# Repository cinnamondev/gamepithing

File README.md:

# Raspberry Pi Handheld (Leviathan)

[Visit the project page!](https://itscinnamon.me/projects/leviathan)

# UPDATE 09/03/2023

This project will likely never be tested or finished now. It is getting increasingly difficult to find a reasonable source of a CM4 to begin and my previously backordered CM4 has since been cancelled without notice.

**Please do not try to make this board, it will probably break something!**

## Loading this project

Clone this project via git
`git clone https://github.com/cinnamondev/gamepithing`

You need Kicad 6+ to load this project.
[KiCad Download](https://www.kicad.org/download/)

## Build it!

Gerber files will be in the releases once this has been properly done- for a BOM read the Wiki (TBD)

## To-do list:
- Snip...

- [ ] Repo clean up
- [ ] CM4 Backorder arrival
- [ ] Extra revisions (general improvements, no additional features)
- [ ] Box/Casing final revision printed (sliding and retention mechanism perfected)
- [ ] Built boards!

## Licensing

Licensed under CERN Open Hardware License v2 - Strongly Reciprocal
[License](LICENSE)

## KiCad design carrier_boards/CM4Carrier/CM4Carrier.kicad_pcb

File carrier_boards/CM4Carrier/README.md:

#   CM4Carrier
Kicad files for the carrier board.

(rev2-slidey): Remaking design to follow best practices.

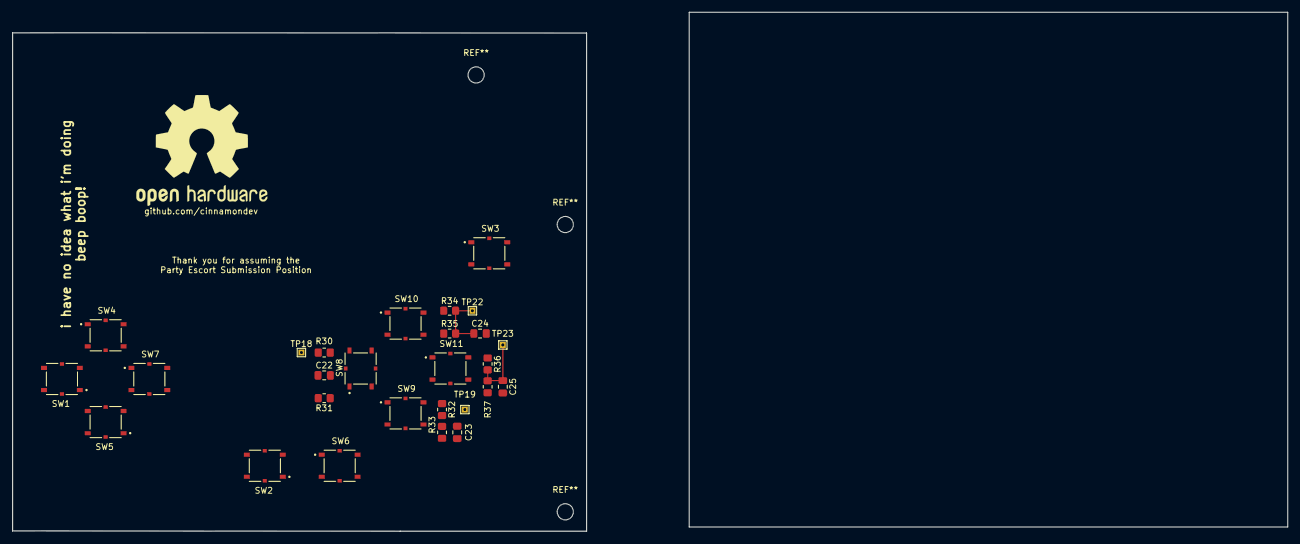
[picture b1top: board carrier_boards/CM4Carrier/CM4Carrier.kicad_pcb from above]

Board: 4 copper layers, 95.9 x 83.3 mm, 27 parts (0 on the bottom side), 10 nets.

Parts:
C22: 100nF; C_0805_2012Metric_Pad1.18x1.45mm_HandSolder
C23, C24, C25: 100n; C_0805_2012Metric_Pad1.18x1.45mm_HandSolder
R30, R32, R34, R36: 1k; R_0805_2012Metric_Pad1.20x1.40mm_HandSolder
R31, R33, R35, R37: 10k; R_0805_2012Metric_Pad1.20x1.40mm_HandSolder
SW1, SW2, SW3, SW4, SW5, SW6, SW7, SW8, SW9, SW10, SW11: SW_Push; SW_PTS526_SMG15_SMTR2_LFS
TP18: A; TestPoint_THTPad_1.0x1.0mm_Drill0.5mm
TP19: X; TestPoint_THTPad_1.0x1.0mm_Drill0.5mm
TP22: B; TestPoint_THTPad_1.0x1.0mm_Drill0.5mm
TP23: Y; TestPoint_THTPad_1.0x1.0mm_Drill0.5mm

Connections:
/3v3: R31.1, R33.1, R35.1, R37.1
/bi6: C22.1, R30.2, R31.2, TP18.1
/bi7: C24.1, R34.2, R35.2, TP22.1
/bi8: C23.1, R32.2, R33.2, TP19.1
/bi9: C25.1, R36.2, R37.2, TP23.1
GND: C22.2, C23.2, C24.2, C25.2, SW1.1, SW2.1, SW3.1, SW4.1, SW5.1, SW6.1, SW7.1, SW8.1, SW9.1, SW10.1, SW11.1
unnamed: R30.1, SW8.2
unnamed: R32.1, SW9.2
unnamed: R34.1, SW10.2
unnamed: R36.1, SW11.2

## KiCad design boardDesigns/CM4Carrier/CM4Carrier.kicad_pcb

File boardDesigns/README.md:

# Board designs

Kicad 6+ is required for these files.
If you want to build this board yourself, I reccomend using the Gerber files built in the Releases section instead. If you want to combine these there are plenty of gerber paneliser softwares available. (Maybe only combine the left shoulder and adaptor as you will likely exceed the JLCPCB sizes).

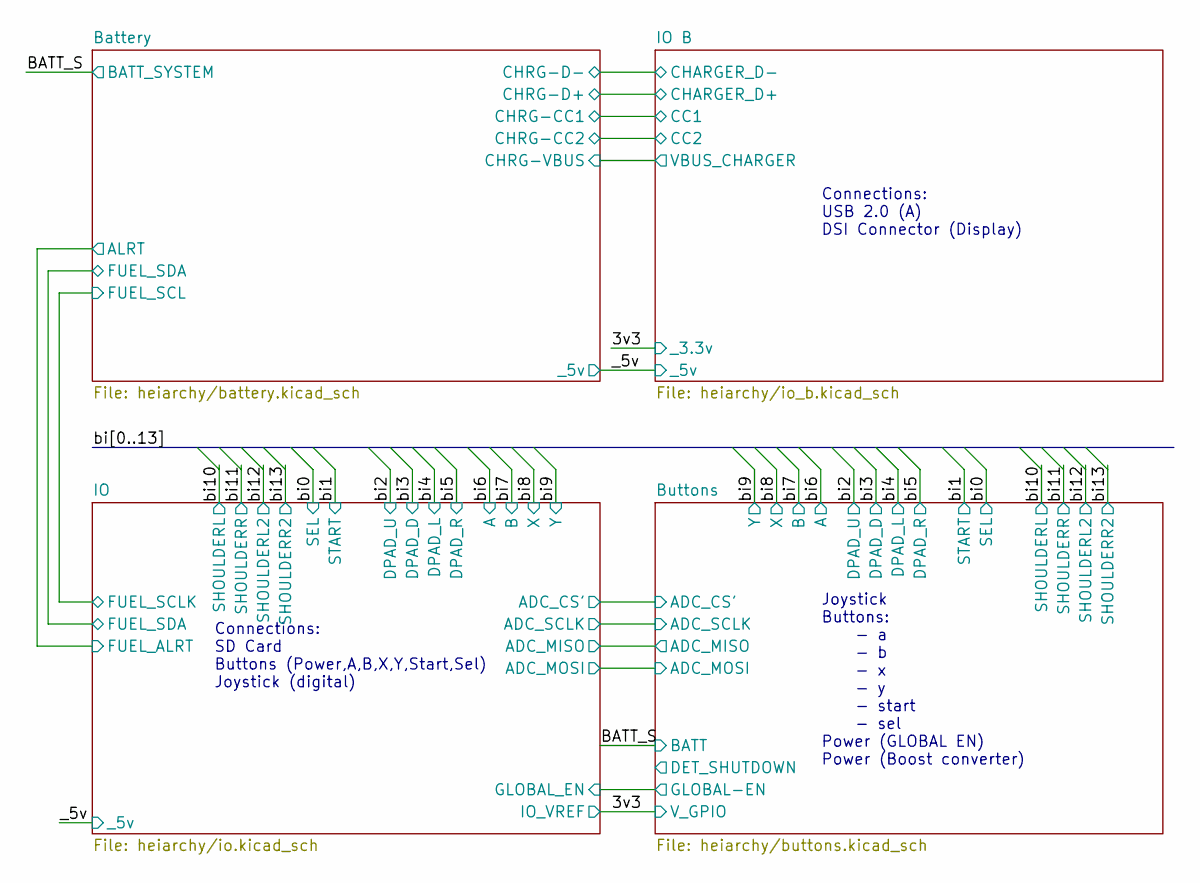
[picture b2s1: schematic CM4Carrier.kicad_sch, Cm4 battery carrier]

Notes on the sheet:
Joystick Buttons: - a - b - x - y - start - sel Power (GLOBAL EN) Power (Boost converter)
Connections: USB 2.0 (A) DSI Connector (Display)
Connections: SD Card Buttons (Power,A,B,X,Y,Start,Sel) Joystick (digital)

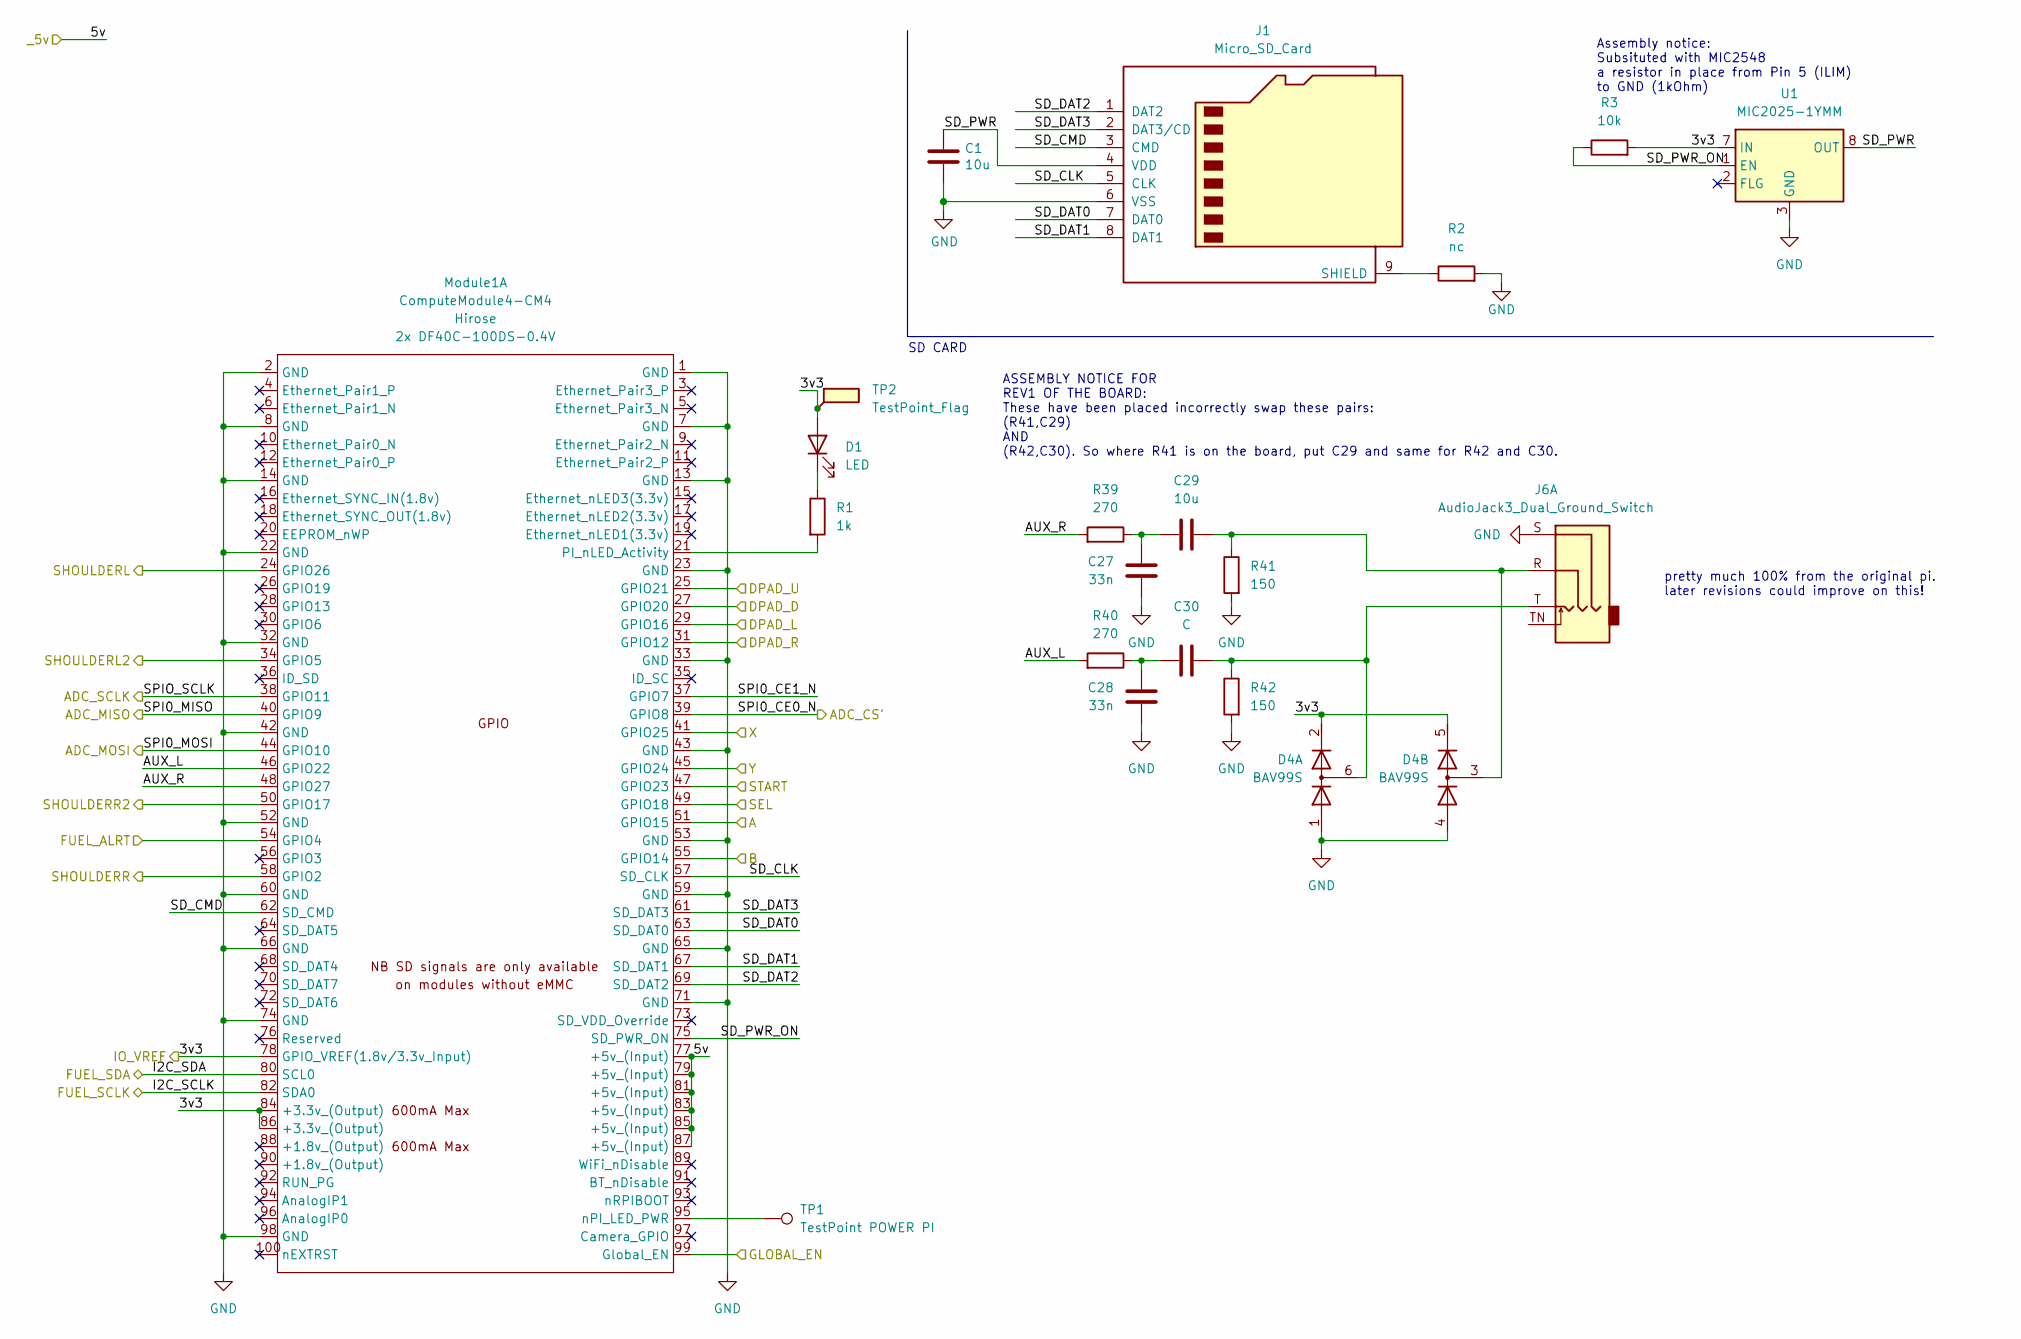
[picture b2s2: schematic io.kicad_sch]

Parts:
C1: 10u; C_0805_2012Metric_Pad1.18x1.45mm_HandSolder; Part Description 10uF 10% 10V Ceramic Capacitor X7R 0805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
C27, C28: 33n; C_0805_2012Metric_Pad1.18x1.45mm_HandSolder
C29: 10u; C_0805_2012Metric_Pad1.18x1.45mm_HandSolder
C30: C; C_0805_2012Metric_Pad1.18x1.45mm_HandSolder
D1: LED; LED_0805_2012Metric_Pad1.15x1.40mm_HandSolder
D4: BAV99S; SOT-363_SC-70-6
J1: Micro_SD_Card; GCT_MEM2067-02-180-00-A_REVB
J6: AudioJack3_Dual_Ground_Switch; Jack_3.5mm_CUI_SJ-3524-SMT_Horizontal
Module1: ComputeModule4-CM4; Raspberry-Pi-4-Compute-Module
R1: 1k; R_0805_2012Metric_Pad1.20x1.40mm_HandSolder
R2: nc; R_0805_2012Metric_Pad1.20x1.40mm_HandSolder
R3: 10k; R_0805_2012Metric_Pad1.20x1.40mm_HandSolder
R39, R40: 270; R_0805_2012Metric_Pad1.20x1.40mm_HandSolder
R41, R42: 150; R_0805_2012Metric_Pad1.20x1.40mm_HandSolder
TP1: TestPoint POWER PI; TestPoint_THTPad_1.0x1.0mm_Drill0.5mm
TP2: TestPoint_Flag; TestPoint_THTPad_1.0x1.0mm_Drill0.5mm
U1: MIC2025-1YMM; MSOP-8_3x3mm_P0.65mm

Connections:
/3v3: D1.2 (A), D4.2 (K2), D4.5 (K4), Module1.78 (GPIO_VREF(1.8v/3.3v_Input)), Module1.84 (+3.3v_(Output)), Module1.86 (+3.3v_(Output)), R3.2, TP2.1, U1.7 (IN); also elsewhere on the board
/Battery/ALRT: Module1.54 (GPIO4); also elsewhere on the board
/Buttons/GLOBAL-EN: Module1.99 (Global_EN); also elsewhere on the board
/IO/AUX_L: Module1.46 (GPIO22), R40.2
/IO/AUX_R: Module1.48 (GPIO27), R39.2
/IO/I2C_SCLK: Module1.82 (SDA0); also elsewhere on the board
/IO/I2C_SDA: Module1.80 (SCL0); also elsewhere on the board
/IO/SD_CLK: J1.5 (CLK), Module1.57 (SD_CLK)
/IO/SD_CMD: J1.3 (CMD), Module1.62 (SD_CMD)
/IO/SD_DAT0: J1.7 (DAT0), Module1.63 (SD_DAT0)
/IO/SD_DAT1: J1.8 (DAT1), Module1.67 (SD_DAT1)
/IO/SD_DAT2: J1.1 (DAT2), Module1.69 (SD_DAT2)
/IO/SD_DAT3: J1.2 (DAT3/CD), Module1.61 (SD_DAT3)
/IO/SD_PWR: C1.1, J1.4 (VDD), U1.6 (OUT), U1.8 (OUT)
/IO/SD_PWR_ON: Module1.75 (SD_PWR_ON), R3.1, U1.1 (EN)
/IO/SPI0_CE0_N: Module1.39 (GPIO8); also elsewhere on the board
/IO/SPI0_CE1_N: Module1.37 (GPIO7)
/IO/SPI0_MISO: Module1.40 (GPIO9); also elsewhere on the board
/IO/SPI0_MOSI: Module1.44 (GPIO10); also elsewhere on the board
/IO/SPIO_SCLK: Module1.38 (GPIO11); also elsewhere on the board
/_5v: Module1.77 (+5v_(Input)), Module1.79 (+5v_(Input)), Module1.81 (+5v_(Input)), Module1.83 (+5v_(Input)), Module1.85 (+5v_(Input)), Module1.87 (+5v_(Input)); also elsewhere on the board
/bi0: Module1.49 (GPIO18); also elsewhere on the board
/bi1: Module1.47 (GPIO23); also elsewhere on the board
/bi2: Module1.25 (GPIO21); also elsewhere on the board
/bi3: Module1.27 (GPIO20); also elsewhere on the board
/bi4: Module1.29 (GPIO16); also elsewhere on the board
/bi5: Module1.31 (GPIO12); also elsewhere on the board
/bi6: Module1.51 (GPIO15); also elsewhere on the board
/bi7: Module1.55 (GPIO14); also elsewhere on the board
/bi8: Module1.41 (GPIO25); also elsewhere on the board
/bi9: Module1.45 (GPIO24); also elsewhere on the board
/bi10: Module1.24 (GPIO26); also elsewhere on the board
/bi11: Module1.58 (GPIO2); also elsewhere on the board
/bi12: Module1.34 (GPIO5); also elsewhere on the board
/bi13: Module1.50 (GPIO17); also elsewhere on the board
unnamed: D1.1 (K), R1.1
unnamed: J1.9 (SHIELD), R2.1
unnamed: Module1.21 (PI_nLED_Activity), R1.2
unnamed: Module1.95 (nPI_LED_PWR), TP1.1

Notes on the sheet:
ASSEMBLY NOTICE FOR REV1 OF THE BOARD: These have been placed incorrectly swap these pairs: (R41,C29) AND (R42,C30). So where R41 is on the board, put C29 and same for R42 and C30.
Assembly notice: Subsituted with MIC2548 a resistor in place from Pin 5 (ILIM) to GND (1kOhm)
pretty much 100% from the original pi. later revisions could improve on this!
SD CARD

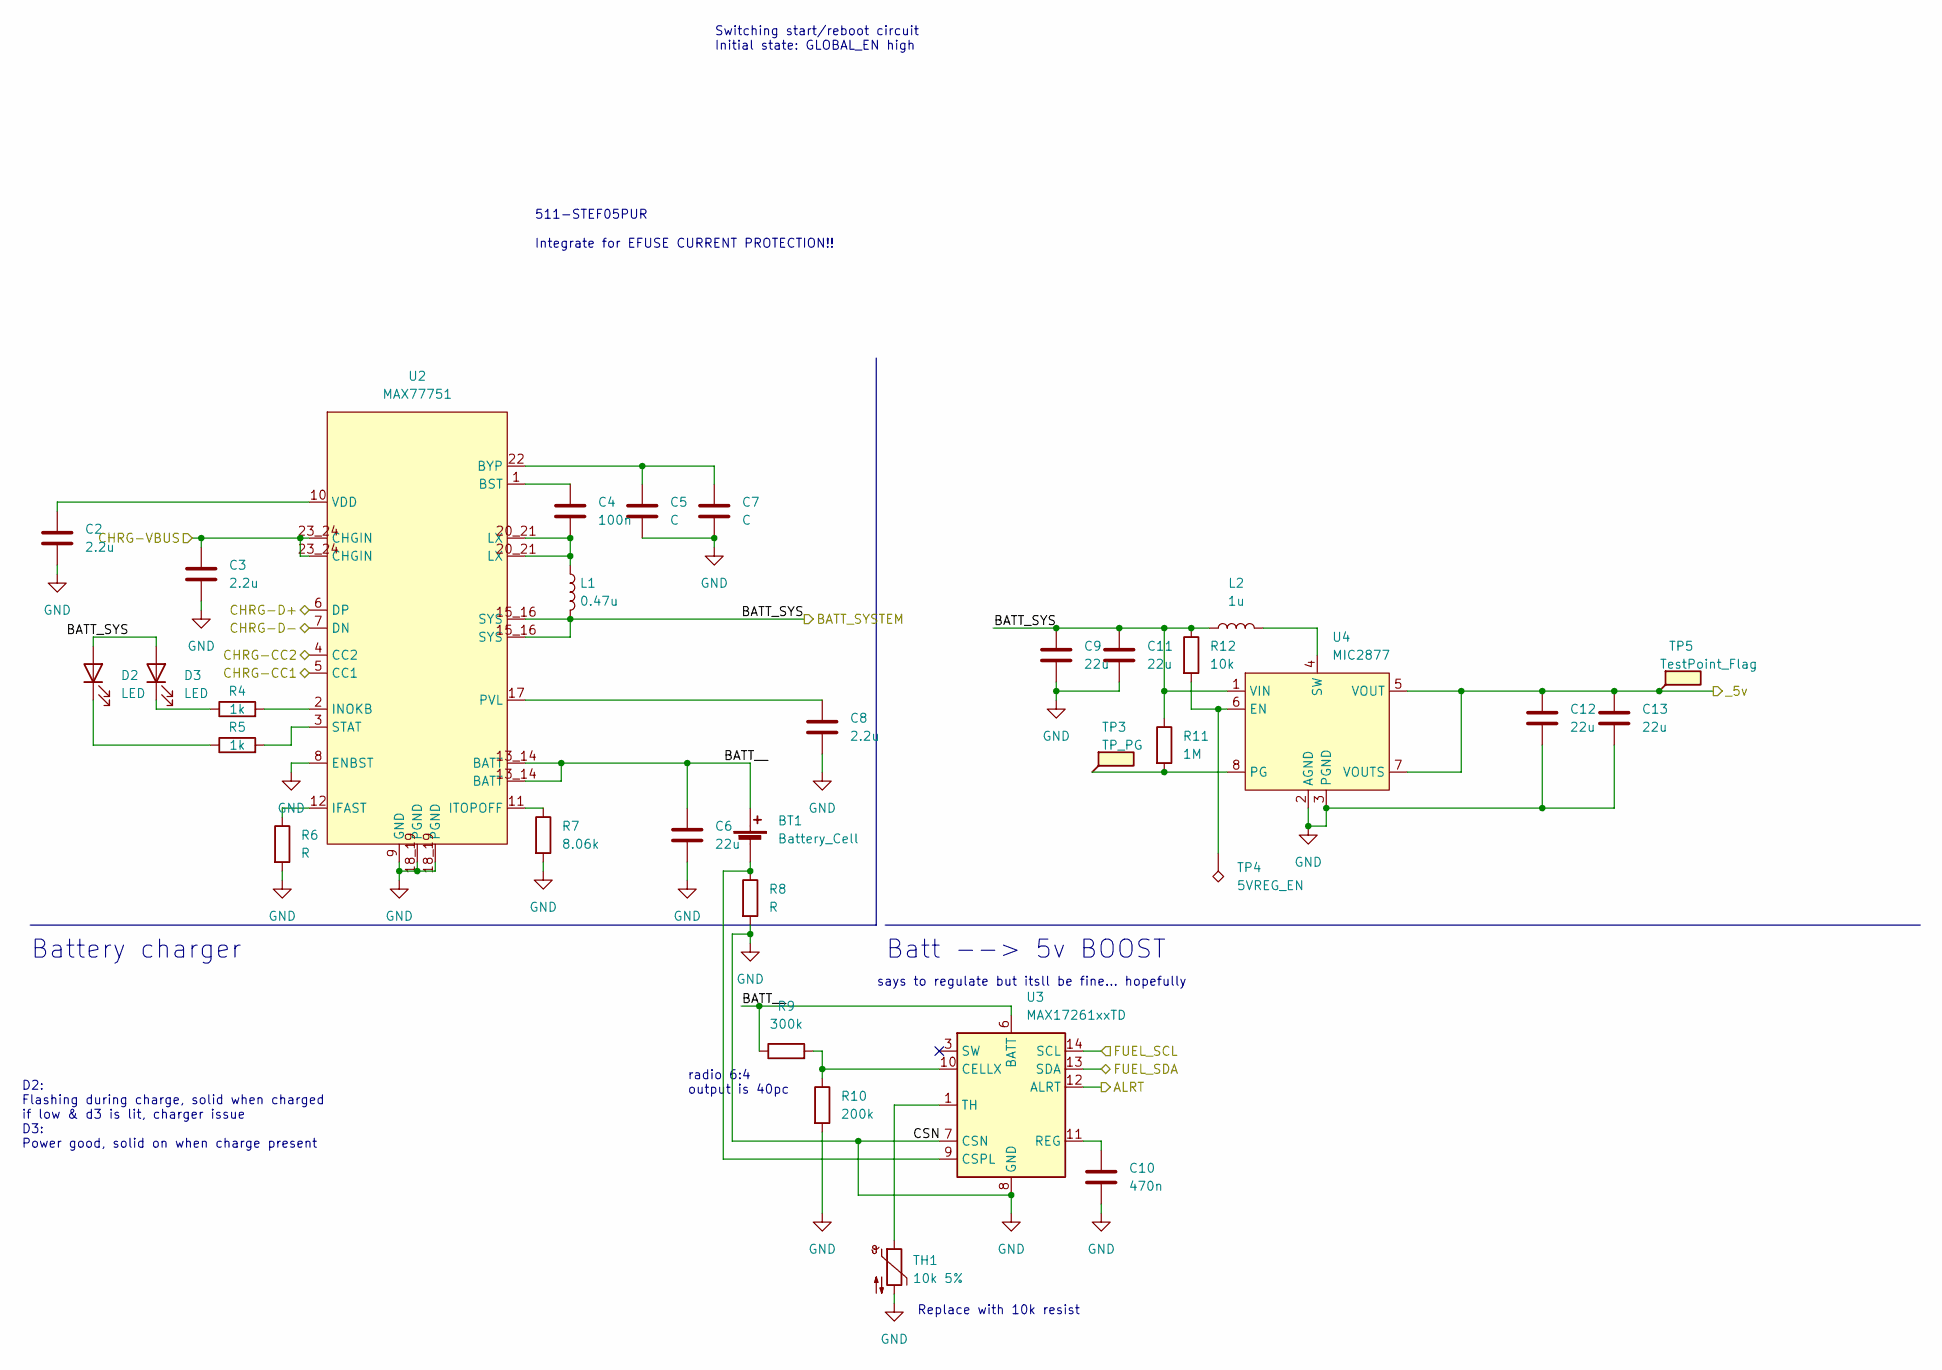
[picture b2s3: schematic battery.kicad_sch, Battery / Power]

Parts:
BT1: Battery_Cell; JST_XH_S2B-XH-A_1x02_P2.50mm_Horizontal
C2, C8: 2.2u; C_0603_1608Metric_Pad1.08x0.95mm_HandSolder
C3: 2.2u; C_0805_2012Metric_Pad1.18x1.45mm_HandSolder
C4: 100n; C_0805_2012Metric_Pad1.18x1.45mm_HandSolder
C5, C7: C; C_0805_2012Metric_Pad1.18x1.45mm_HandSolder
C6, C9, C11, C12, C13: 22u; C_0805_2012Metric_Pad1.18x1.45mm_HandSolder
C10: 470n; C_0603_1608Metric_Pad1.08x0.95mm_HandSolder
D2, D3: LED; LED_0805_2012Metric_Pad1.15x1.40mm_HandSolder
L1: 0.47u; L_1008_2520Metric_Pad1.43x2.20mm_HandSolder
L2: 1u; L_1008_2520Metric_Pad1.43x2.20mm_HandSolder
R4, R5: 1k; R_0805_2012Metric_Pad1.20x1.40mm_HandSolder
R6: R; R_0603_1608Metric_Pad0.98x0.95mm_HandSolder
R7: 8.06k; R_0603_1608Metric_Pad0.98x0.95mm_HandSolder
R8: R; R_0805_2012Metric_Pad1.20x1.40mm_HandSolder
R9: 300k; R_0603_1608Metric_Pad0.98x0.95mm_HandSolder
R10: 200k; R_0603_1608Metric_Pad0.98x0.95mm_HandSolder
R11: 1M; R_0805_2012Metric_Pad1.20x1.40mm_HandSolder
R12: 10k; R_0805_2012Metric_Pad1.20x1.40mm_HandSolder
TH1: 10k 5%; R_0805_2012Metric_Pad1.20x1.40mm_HandSolder
TP3: TP_PG; TestPoint_THTPad_1.0x1.0mm_Drill0.5mm
TP4: 5VREG_EN; TestPoint_THTPad_1.0x1.0mm_Drill0.5mm
TP5: TestPoint_Flag; TestPoint_THTPad_1.0x1.0mm_Drill0.5mm
U2: MAX77751; IC_MAX77751FEFG+
U3: MAX17261xxTD; TDFN-14-1EP_3x3mm_P0.4mm_EP1.78x2.35mm
U4: MIC2877; MIC2877-AYFT-TR

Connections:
/BATT_S: C9.1, C11.1, D2.2 (A), D3.2 (A), L1.2, L2.1, R11.1, R12.1, U2.15_16 (SYS), U4.1 (VIN); also elsewhere on the board
/Battery/ALRT: U3.12 (ALRT); also elsewhere on the board
/Battery/BATT__: BT1.1 (+), C6.1, R9.1, U2.13_14 (BATT), U3.6 (BATT)
/Battery/CHRG-CC1: U2.5 (CC1); also elsewhere on the board
/Battery/CHRG-CC2: U2.4 (CC2); also elsewhere on the board
/Battery/CHRG-D+: U2.6 (DP); also elsewhere on the board
/Battery/CHRG-D-: U2.7 (DN); also elsewhere on the board
/Battery/CHRG-VBUS: C3.1, U2.23_24 (CHGIN); also elsewhere on the board
/IO/I2C_SCLK: U3.14 (SCL); also elsewhere on the board
/IO/I2C_SDA: U3.13 (SDA); also elsewhere on the board
/_5v: C12.1, C13.1, TP5.1, U4.5 (VOUT), U4.7 (VOUTS); also elsewhere on the board
unnamed: BT1.2 (-), R8.1, U3.9 (CSPL)
unnamed: C2.1, U2.10 (VDD)
unnamed: C4.1, U2.1 (BST)
unnamed: C4.2, L1.1, U2.20_21 (LX)
unnamed: C5.1, C7.1, U2.22 (BYP)
unnamed: C8.1, U2.17 (PVL)
unnamed: C10.1, U3.11 (REG)
unnamed: D2.1 (K), R5.1
unnamed: D3.1 (K), R4.1
unnamed: L2.2, U4.4 (SW)
unnamed: R4.2, U2.2 (INOKB)
unnamed: R5.2, U2.3 (STAT)
unnamed: R6.1, U2.12 (IFAST)
unnamed: R7.1, U2.11 (ITOPOFF)
unnamed: R9.2, R10.1, U3.10 (CELLX)
unnamed: R11.2, TP3.1, U4.8 (PG)
unnamed: R12.2, TP4.1, U4.6 (EN)
unnamed: TH1.1, U3.1 (TH)

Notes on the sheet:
Batt --> 5v BOOST
Battery charger
Switching start/reboot circuit Initial state: GLOBAL_EN high
says to regulate but itsll be fine... hopefully
radio 6:4 output is 40pc
511-STEF05PUR Integrate for EFUSE CURRENT PROTECTION!!
Replace with 10k resist
D2: Flashing during charge, solid when charged if low & d3 is lit, charger issue D3: Power good, solid on when charge present

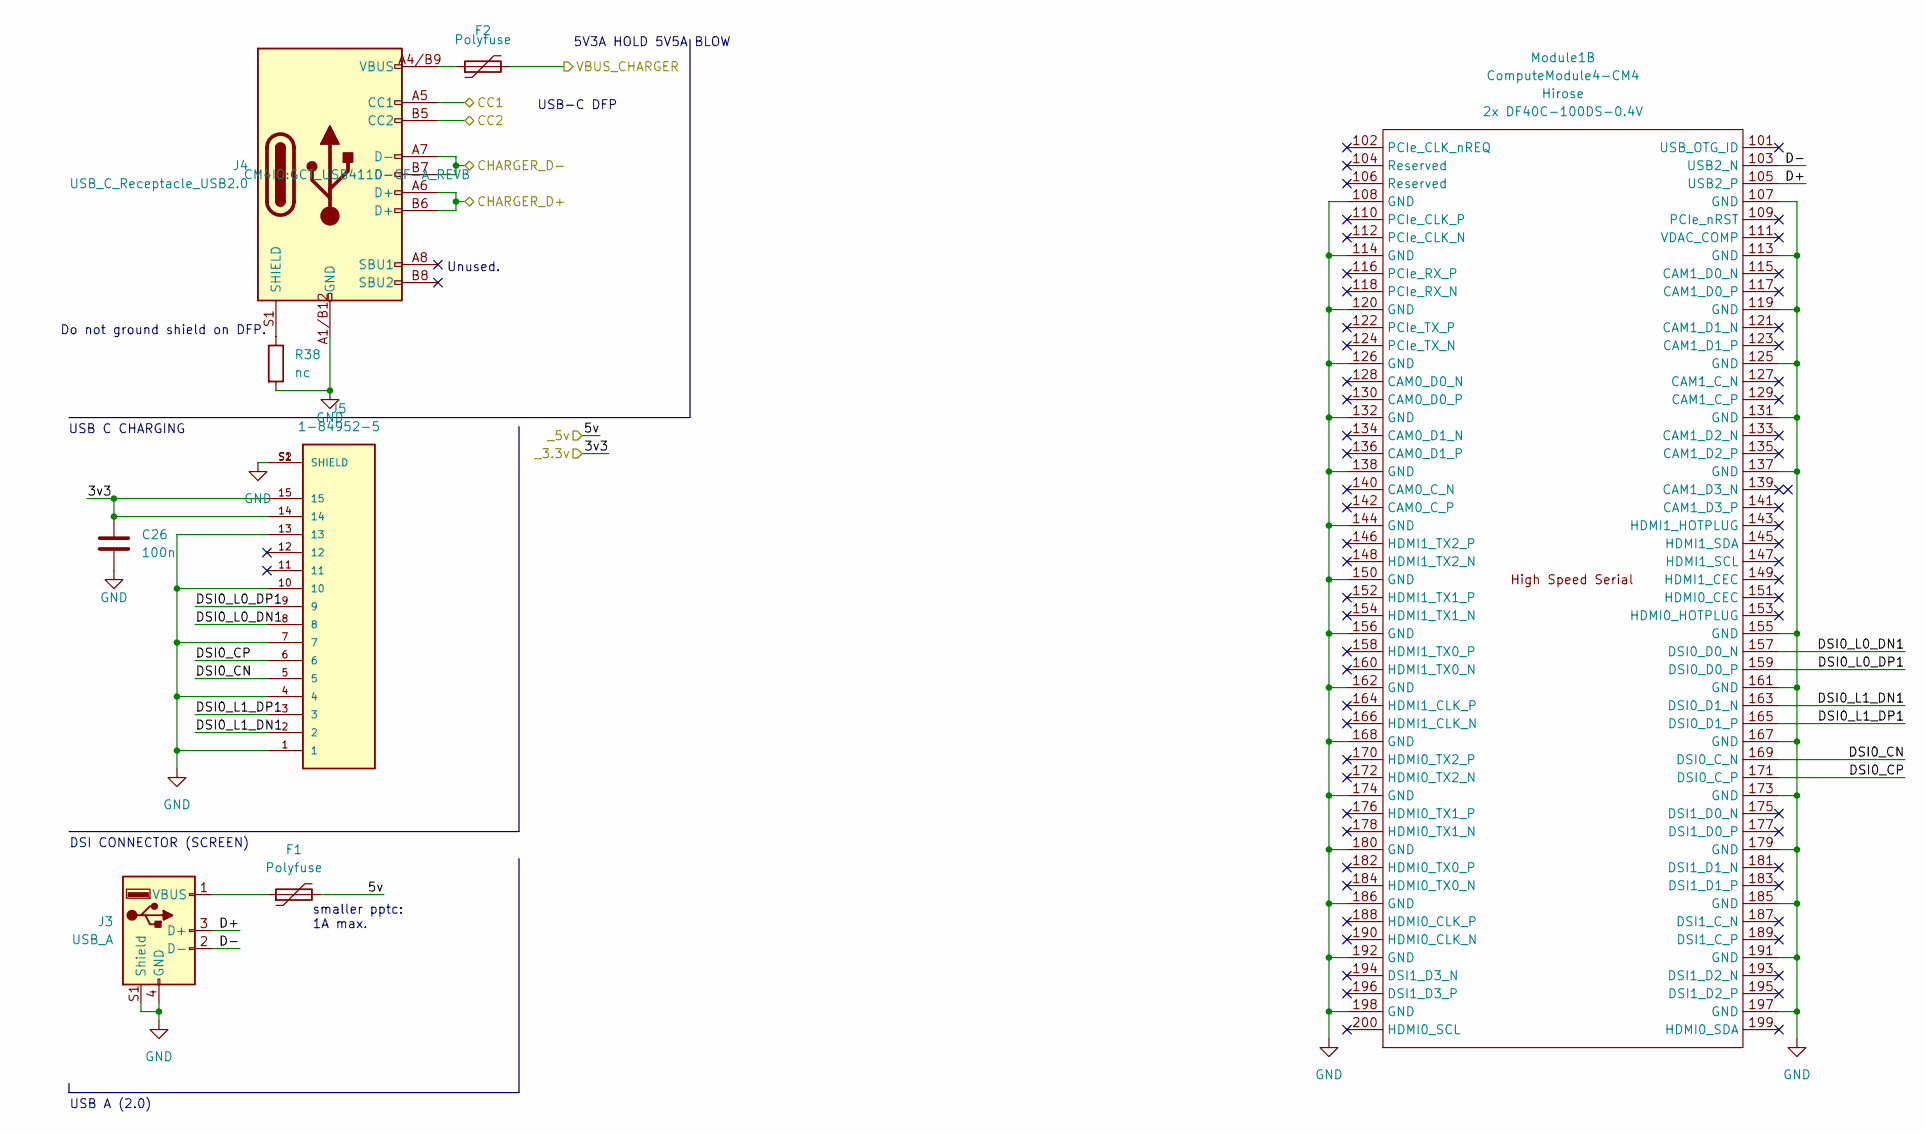
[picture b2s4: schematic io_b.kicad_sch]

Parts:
C26: 100n; C_0805_2012Metric_Pad1.18x1.45mm_HandSolder
F1: Polyfuse; Fuse_1210_3225Metric_Pad1.42x2.65mm_HandSolder
F2: Polyfuse; Fuse_0805_2012Metric_Pad1.15x1.40mm_HandSolder
J3: USB_A; GCT_USB1125-GF-B_REVA
J4: USB_C_Receptacle_USB2.0; GCT_USB4110-GF-A_REVB
J5: 1-84952-5; TE_1-84952-5
Module1: ComputeModule4-CM4; Raspberry-Pi-4-Compute-Module
R38: nc; R_0805_2012Metric_Pad1.20x1.40mm_HandSolder

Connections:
/3v3: C26.1, J5.14, J5.15; also elsewhere on the board
/Battery/CHRG-CC1: J4.A5 (CC1); also elsewhere on the board
/Battery/CHRG-CC2: J4.B5 (CC2); also elsewhere on the board
/Battery/CHRG-D+: J4.A6 (D+), J4.B6 (D+); also elsewhere on the board
/Battery/CHRG-D-: J4.A7 (D-), J4.B7 (D-); also elsewhere on the board
/Battery/CHRG-VBUS: F2.2; also elsewhere on the board
/IO B/D+: J3.3 (D+), Module1.105 (USB2_P)
/IO B/D-: J3.2 (D-), Module1.103 (USB2_N)
/IO B/DSI0_CN: J5.5, Module1.169 (DSI0_C_N)
/IO B/DSI0_CP: J5.6, Module1.171 (DSI0_C_P)
/IO B/DSI0_L0_DN1: J5.8, Module1.157 (DSI0_D0_N)
/IO B/DSI0_L0_DP1: J5.9, Module1.159 (DSI0_D0_P)
/IO B/DSI0_L1_DN1: J5.2, Module1.163 (DSI0_D1_N)
/IO B/DSI0_L1_DP1: J5.3, Module1.165 (DSI0_D1_P)
/_5v: F1.2; also elsewhere on the board
unnamed: F1.1, J3.1 (VBUS)
unnamed: F2.1, J4.A4/B9 (VBUS), J4.B4/A9 (VBUS)
unnamed: J4.S1 (SHIELD), R38.1

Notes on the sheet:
USB A (2.0)
smaller pptc: 1A max.
DSI CONNECTOR (SCREEN)
Unused.
5V3A HOLD 5V5A BLOW
USB-C DFP
USB C CHARGING
Do not ground shield on DFP.

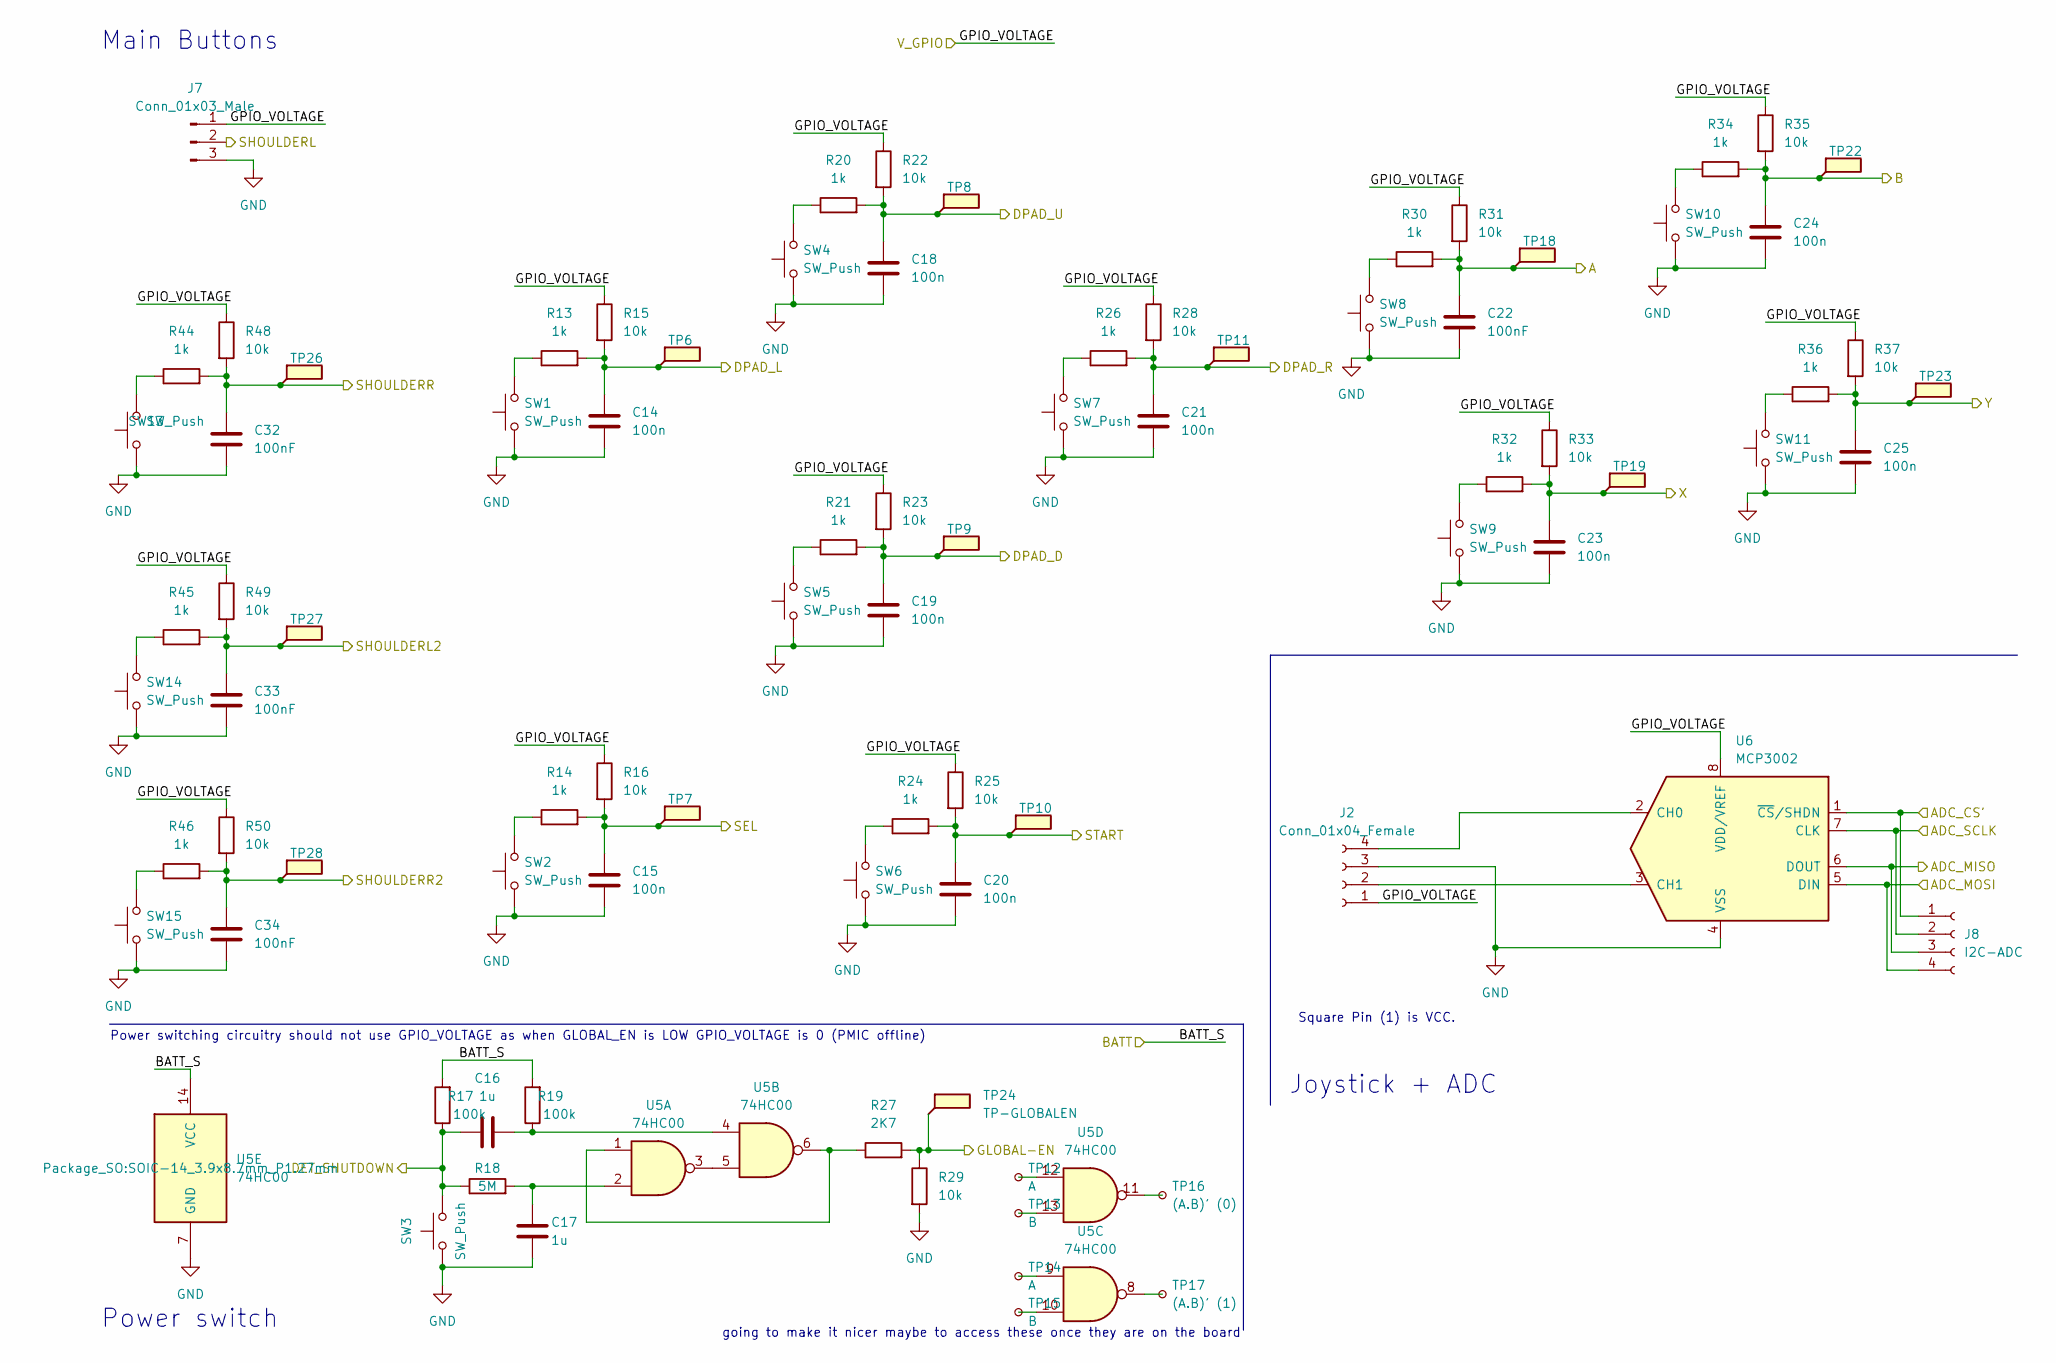
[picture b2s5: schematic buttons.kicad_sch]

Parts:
C14, C15, C18, C19, C20, C21, C23, C24, C25: 100n; C_0805_2012Metric_Pad1.18x1.45mm_HandSolder
C16, C17: 1u; C_0805_2012Metric_Pad1.18x1.45mm_HandSolder
C22, C32, C33, C34: 100nF; C_0805_2012Metric_Pad1.18x1.45mm_HandSolder
J2: Conn_01x04_Female; SolderWire-0.1sqmm_1x04_P3.6mm_D0.4mm_OD1mm
J7: Conn_01x03_Male; SolderWire-0.5sqmm_1x03_P4.8mm_D0.9mm_OD2.3mm
J8: I2C-ADC; SolderWire-0.1sqmm_1x04_P3.6mm_D0.4mm_OD1mm
R13, R14, R20, R21, R24, R26, R30, R32, R34, R36, R44, R45, R46: 1k; R_0805_2012Metric_Pad1.20x1.40mm_HandSolder
R15, R16, R22, R23, R25, R28, R29, R31, R33, R35, R37, R48, R49, R50: 10k; R_0805_2012Metric_Pad1.20x1.40mm_HandSolder
R17, R19: 100k; R_0805_2012Metric_Pad1.20x1.40mm_HandSolder
R18: 5M; R_0805_2012Metric_Pad1.20x1.40mm_HandSolder
R27: 2K7; R_0805_2012Metric_Pad1.20x1.40mm_HandSolder
SW1, SW2, SW3, SW4, SW5, SW6, SW7, SW8, SW9, SW10, SW11, SW14, SW15: SW_Push; SW_PTS526_SMG15_SMTR2_LFS
SW13: SW_Push; SW_EVQ-P7J01P
TP6: L; TestPoint_THTPad_1.0x1.0mm_Drill0.5mm
TP7: SEL; TestPoint_THTPad_1.0x1.0mm_Drill0.5mm
TP8: U; TestPoint_THTPad_1.0x1.0mm_Drill0.5mm
TP9: D; TestPoint_THTPad_1.0x1.0mm_Drill0.5mm
TP10: START; TestPoint_THTPad_1.0x1.0mm_Drill0.5mm
TP11: R; TestPoint_THTPad_1.0x1.0mm_Drill0.5mm
TP12, TP14, TP18, TP26, TP27, TP28: A; TestPoint_THTPad_1.0x1.0mm_Drill0.5mm
TP13, TP15, TP22: B; TestPoint_THTPad_1.0x1.0mm_Drill0.5mm
TP16: (A.B)' (0); TestPoint_THTPad_1.0x1.0mm_Drill0.5mm
TP17: (A.B)' (1); TestPoint_THTPad_1.0x1.0mm_Drill0.5mm
TP19: X; TestPoint_THTPad_1.0x1.0mm_Drill0.5mm
TP23: Y; TestPoint_THTPad_1.0x1.0mm_Drill0.5mm
TP24: TP-GLOBALEN; TestPoint_THTPad_1.0x1.0mm_Drill0.5mm
U5: 74HC00; SOIC-14_3.9x8.7mm_P1.27mm
U6: MCP3002; TSSOP-8_4.4x3mm_P0.65mm

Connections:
/3v3: J2.1, J7.1, R15.1, R16.1, R22.1, R23.1, R25.1, R28.1, R31.1, R33.1, R35.1, R37.1, R48.1, R49.1, R50.1, U6.8 (VDD/VREF); also elsewhere on the board
/BATT_S: R17.2, R19.2, U5.14 (VCC); also elsewhere on the board
/Buttons/DET_SHUTDOWN: C16.1, R17.1, R18.1, SW3.2
/Buttons/GLOBAL-EN: R27.2, R29.1, TP24.1; also elsewhere on the board
/IO/SPI0_CE0_N: J8.1, U6.1 (~CS/SHDN); also elsewhere on the board
/IO/SPI0_MISO: J8.3, U6.6 (DOUT); also elsewhere on the board
/IO/SPI0_MOSI: J8.4, U6.5 (DIN); also elsewhere on the board
/IO/SPIO_SCLK: J8.2, U6.7 (CLK); also elsewhere on the board
/bi0: C15.1, R14.2, R16.2, TP7.1; also elsewhere on the board
/bi1: C20.1, R24.2, R25.2, TP10.1; also elsewhere on the board
/bi2: C18.1, R20.2, R22.2, TP8.1; also elsewhere on the board
/bi3: C19.1, R21.2, R23.2, TP9.1; also elsewhere on the board
/bi4: C14.1, R13.2, R15.2, TP6.1; also elsewhere on the board
/bi5: C21.1, R26.2, R28.2, TP11.1; also elsewhere on the board
/bi6: C22.1, R30.2, R31.2, TP18.1; also elsewhere on the board
/bi7: C24.1, R34.2, R35.2, TP22.1; also elsewhere on the board
/bi8: C23.1, R32.2, R33.2, TP19.1; also elsewhere on the board
/bi9: C25.1, R36.2, R37.2, TP23.1; also elsewhere on the board
/bi10: J7.2; also elsewhere on the board
/bi11: C32.1, R44.2, R48.2, TP26.1; also elsewhere on the board
/bi12: C33.1, R45.2, R49.2, TP27.1; also elsewhere on the board
/bi13: C34.1, R46.2, R50.2, TP28.1; also elsewhere on the board
unnamed: C16.2, R19.1, U5.4
unnamed: C17.1, R18.2, U5.2
unnamed: J2.2, U6.3 (CH1)
unnamed: J2.4, U6.2 (CH0)
unnamed: R13.1, SW1.2
unnamed: R14.1, SW2.2
unnamed: R20.1, SW4.2
unnamed: R21.1, SW5.2
unnamed: R24.1, SW6.2
unnamed: R26.1, SW7.2
unnamed: R27.1, U5.1, U5.6
unnamed: R30.1, SW8.2
unnamed: R32.1, SW9.2
unnamed: R34.1, SW10.2
unnamed: R36.1, SW11.2
unnamed: R44.1, SW13.2_1 (2), SW13.2_2 (2)
unnamed: R45.1, SW14.2
unnamed: R46.1, SW15.2
unnamed: TP12.1, U5.12
unnamed: TP13.1, U5.13
unnamed: TP14.1, U5.9
unnamed: TP15.1, U5.10
unnamed: TP16.1, U5.11
unnamed: TP17.1, U5.8
unnamed: U5.3, U5.5

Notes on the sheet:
Joystick + ADC
going to make it nicer maybe to access these once they are on the board
Power switching circuitry should not use GPIO_VOLTAGE as when GLOBAL_EN is LOW GPIO_VOLTAGE is 0 (PMIC offline)
Square Pin (1) is VCC.
Main Buttons
Power switch

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

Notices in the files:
parts and their libraries:
Copyright 2021 Accelerated Designs. All rights reserved.
